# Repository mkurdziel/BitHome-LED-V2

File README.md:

# BitHome-LED-V1
BitHome LED Arduino Zigbee V1

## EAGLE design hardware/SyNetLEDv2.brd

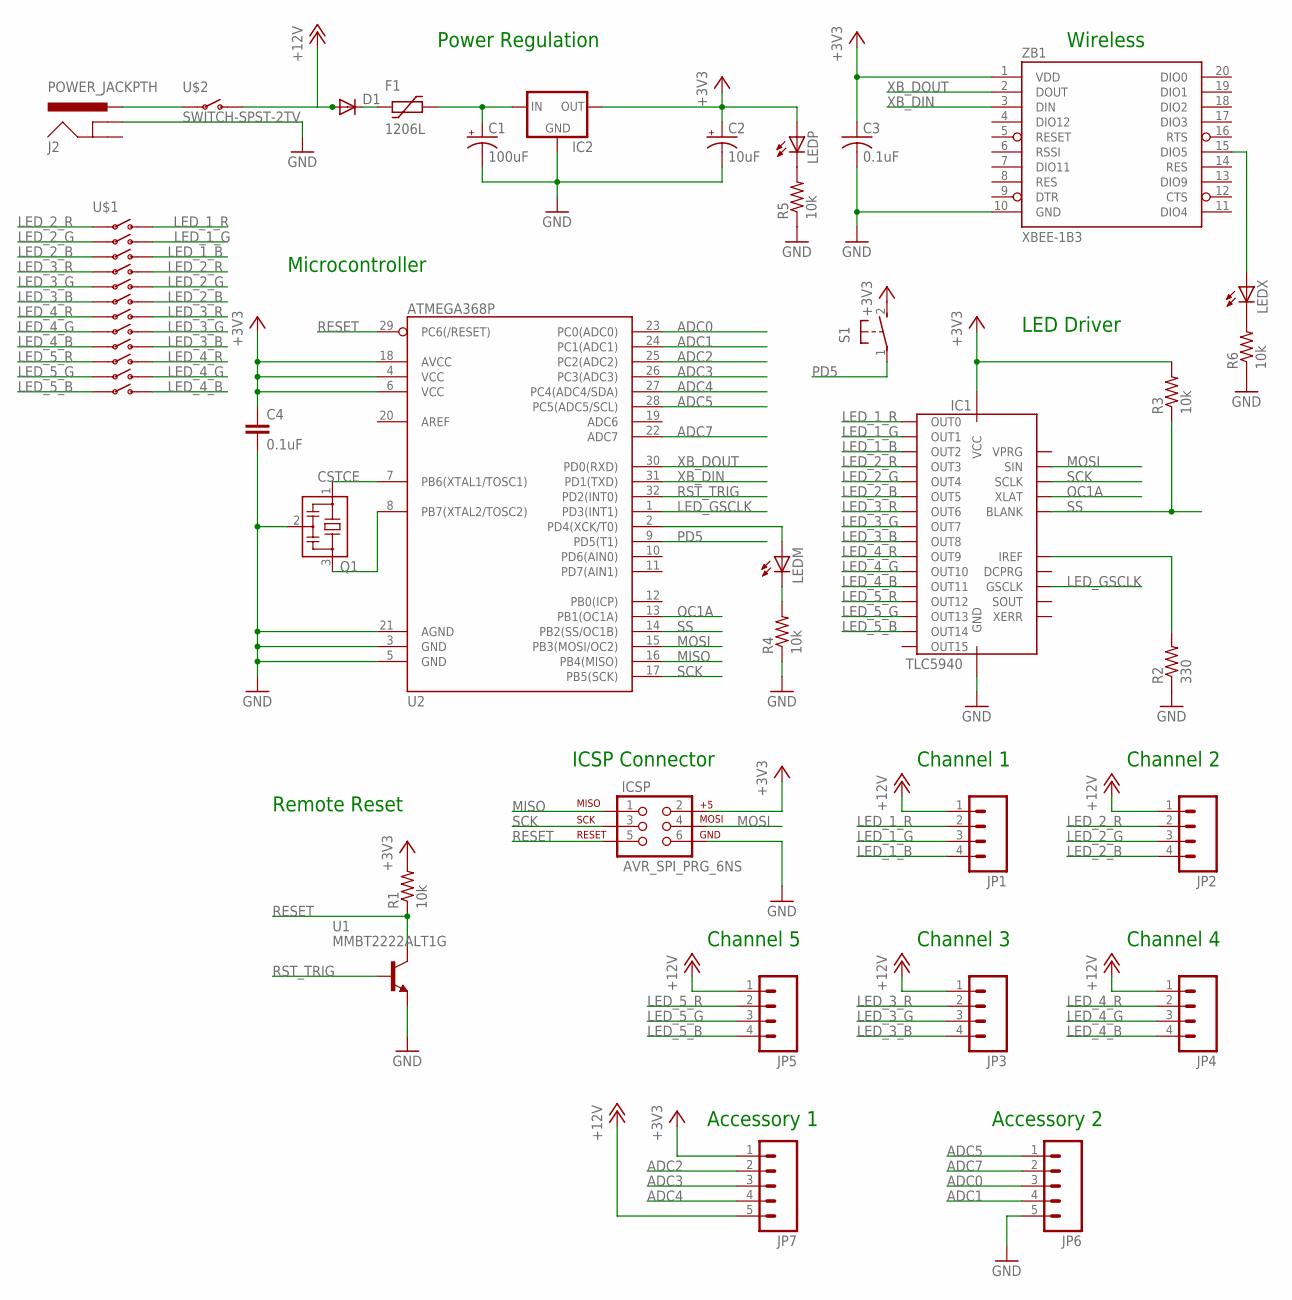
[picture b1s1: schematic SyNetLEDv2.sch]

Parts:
C1: 100uF; UD-8X10_NICHICON
C2: 10uF; UD-4X5,8_NICHICON
C3: 0.1uF; C1608
C4: 0.1uF; 0603-CAP
D1: DIODESOD; SOD-323
F1: 1206L
IC1: TLC5940; HTSSOP28PWP
IC2: 78LXXSMD; SOT223
ICSP: AVR_SPI_PRG_6NS; 2X3-NS
J2: POWER_JACKPTH; POWER_JACK_PTH
JP1, JP2, JP3, JP4, JP5: M04POLAR; MOLEX-1X4
JP6, JP7: M05PTH; 1X05
LEDM: LEDSMT-RT; LED-SMT-RT
LEDP: LEDSMT-RT; LED-SMT-RT
LEDX: LEDSMT-RT; LED-SMT-RT
Q1: CSTCE; CSTCE8
R1, R3, R4, R5, R6: 10k; 0603-RES
R2: 330; 0603-RES
S1: 31-XX; B3F-31XX
U1: MMBT2222ALT1G; SOT23
U2: ATMEGA368P; TQFP32-08
U$1: DIP12DIP12TH; DIP12TH
U$2: SWITCH-SPST-2TV; SWITCH-SPST-VERTICAL
ZB1: XBEE-1B3; XBEE-SMD

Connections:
+3V3: C2.+, C3.1, C4.1, IC1.28 (VCC), IC2.3 (OUT), ICSP.2, JP7.1, LEDP.P$1A (A), R1.2, R3.2, S1.2 (S), U2.4 (VCC), U2.6 (VCC), U2.18 (AVCC), ZB1.1 (VDD)
+12V: D1.2 (A), JP1.1, JP2.1, JP3.1, JP4.1, JP5.1, JP7.5, U$2.1 (O)
ADC0: JP6.3, U2.23 (PC0(ADC0))
ADC1: JP6.4, U2.24 (PC1(ADC1))
ADC2: JP7.2, U2.25 (PC2(ADC2))
ADC3: JP7.3, U2.26 (PC3(ADC3))
ADC4: JP7.4, U2.27 (PC4(ADC4/SDA))
ADC5: JP6.1, U2.28 (PC5(ADC5/SCL))
ADC7: JP6.2, U2.22 (ADC7)
GND: C1.-, C2.-, C3.2, C4.2, IC1.1 (GND), IC2.2 (GND), IC2.4 (GND), ICSP.6, J2.GNDBREAK, JP6.5, Q1.2, R2.1, R4.1, R5.1, R6.1, U1.2 (E), U2.3 (GND), U2.5 (GND), U2.21 (AGND), ZB1.10 (GND)
LED_1_B: IC1.9 (OUT2), JP1.4, U$1.P$3 (P3B)
LED_1_G: IC1.8 (OUT1), JP1.3, U$1.P$2 (P2B)
LED_1_R: IC1.7 (OUT0), JP1.2, U$1.P$1 (P1B)
LED_2_B: IC1.12 (OUT5), JP2.4, U$1.O$3 (P3A), U$1.P$6 (P6B)
LED_2_G: IC1.11 (OUT4), JP2.3, U$1.O$2 (P2A), U$1.P$5 (P5B)
LED_2_R: IC1.10 (OUT3), JP2.2, U$1.O$1 (P1A), U$1.P$4 (P4B)
LED_3_B: IC1.15 (OUT8), JP3.4, U$1.O$6 (P6A), U$1.P$9 (P9B)
LED_3_G: IC1.14 (OUT7), JP3.3, U$1.O$5 (P5A), U$1.P$8 (P8B)
LED_3_R: IC1.13 (OUT6), JP3.2, U$1.O$4 (P4A), U$1.P$7 (P7B)
LED_4_B: IC1.18 (OUT11), JP4.4, U$1.O$9 (P9A), U$1.P$12 (P12B)
LED_4_G: IC1.17 (OUT10), JP4.3, U$1.O$8 (P8A), U$1.P$11 (P11B)
LED_4_R: IC1.16 (OUT9), JP4.2, U$1.O$7 (P7A), U$1.P$10 (P10B)
LED_5_B: IC1.21 (OUT14), JP5.4, U$1.O$12 (P12A)
LED_5_G: IC1.20 (OUT13), JP5.3, U$1.O$11 (P11A)
LED_5_R: IC1.19 (OUT12), JP5.2, U$1.O$10 (P10A)
LED_GSCLK: IC1.25 (GSCLK), U2.1 (PD3(INT1))
MISO: ICSP.1, U2.16 (PB4(MISO))
MOSI: IC1.5 (SIN), ICSP.4, U2.15 (PB3(MOSI/OC2))
unnamed: Q1.1, U2.7 (PB6(XTAL1/TOSC1))
unnamed: Q1.3, U2.8 (PB7(XTAL2/TOSC2))
unnamed: LEDM.P$1A (A), U2.2 (PD4(XCK/T0))
unnamed: D1.1 (C), F1.P$1 (1)
unnamed: C1.+, F1.P$2 (2), IC2.1 (IN)
unnamed: IC1.27 (IREF), R2.2
unnamed: LEDM.P$2C (C), R4.2
unnamed: LEDX.P$2C (C), R6.2
unnamed: LEDP.P$2C (C), R5.2
unnamed: LEDX.P$1A (A), ZB1.15 (DIO5)
unnamed: J2.PWR, U$2.2
OC1A: IC1.3 (XLAT), U2.13 (PB1(OC1A))
PD5: S1.1, U2.9 (PD5(T1))
RESET: ICSP.5, R1.1, U1.3 (C), U2.29 (PC6(/RESET))
RST_TRIG: U1.1 (B), U2.32 (PD2(INT0))
SCK: IC1.4 (SCLK), ICSP.3, U2.17 (PB5(SCK))
SS: IC1.2 (BLANK), R3.1, U2.14 (PB2(SS/OC1B))
XB_DIN: U2.31 (PD1(TXD)), ZB1.3 (DIN)
XB_DOUT: U2.30 (PD0(RXD)), ZB1.2 (DOUT)

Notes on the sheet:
Channel 1
Channel 2
Channel 3
Channel 4
Channel 5
ICSP Connector
Remote Reset
Microcontroller
Power Regulation
Wireless
LED Driver
Accessory 1
Accessory 2

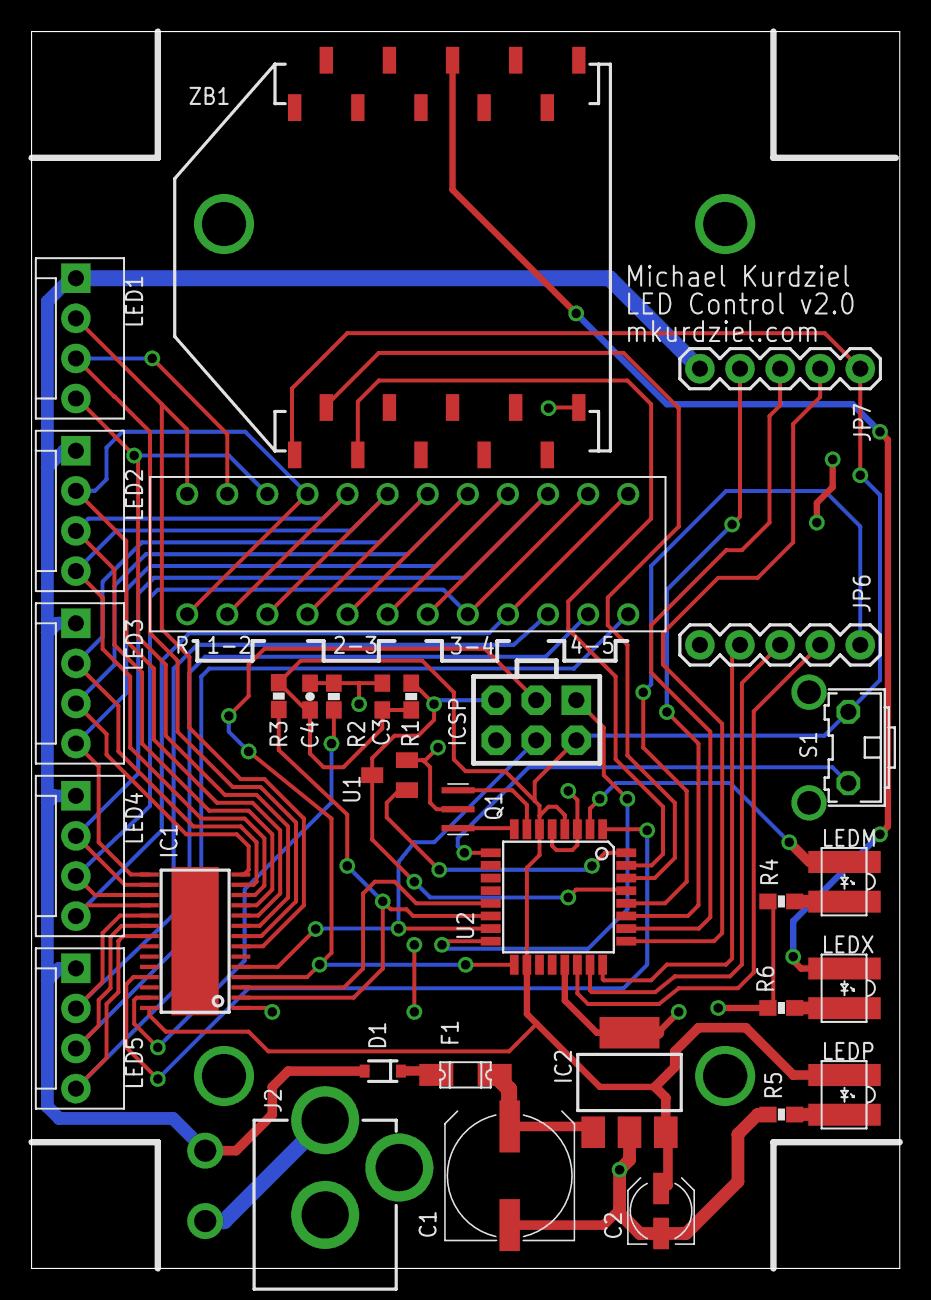
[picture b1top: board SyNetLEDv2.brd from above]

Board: 2 copper layers, 55.0 x 78.4 mm, 33 parts (0 on the bottom side), 47 nets.

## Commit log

2015-12-23 Initial checkin of software
2015-12-23 Hardware

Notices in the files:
parts and their libraries:
SparkFun-Connectors: Licensing: CC v3.0 Share-Alike You are welcome to use this library for commercial purposes.
